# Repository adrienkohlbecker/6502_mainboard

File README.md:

# 6502 mainboard

## Board

## Schematic

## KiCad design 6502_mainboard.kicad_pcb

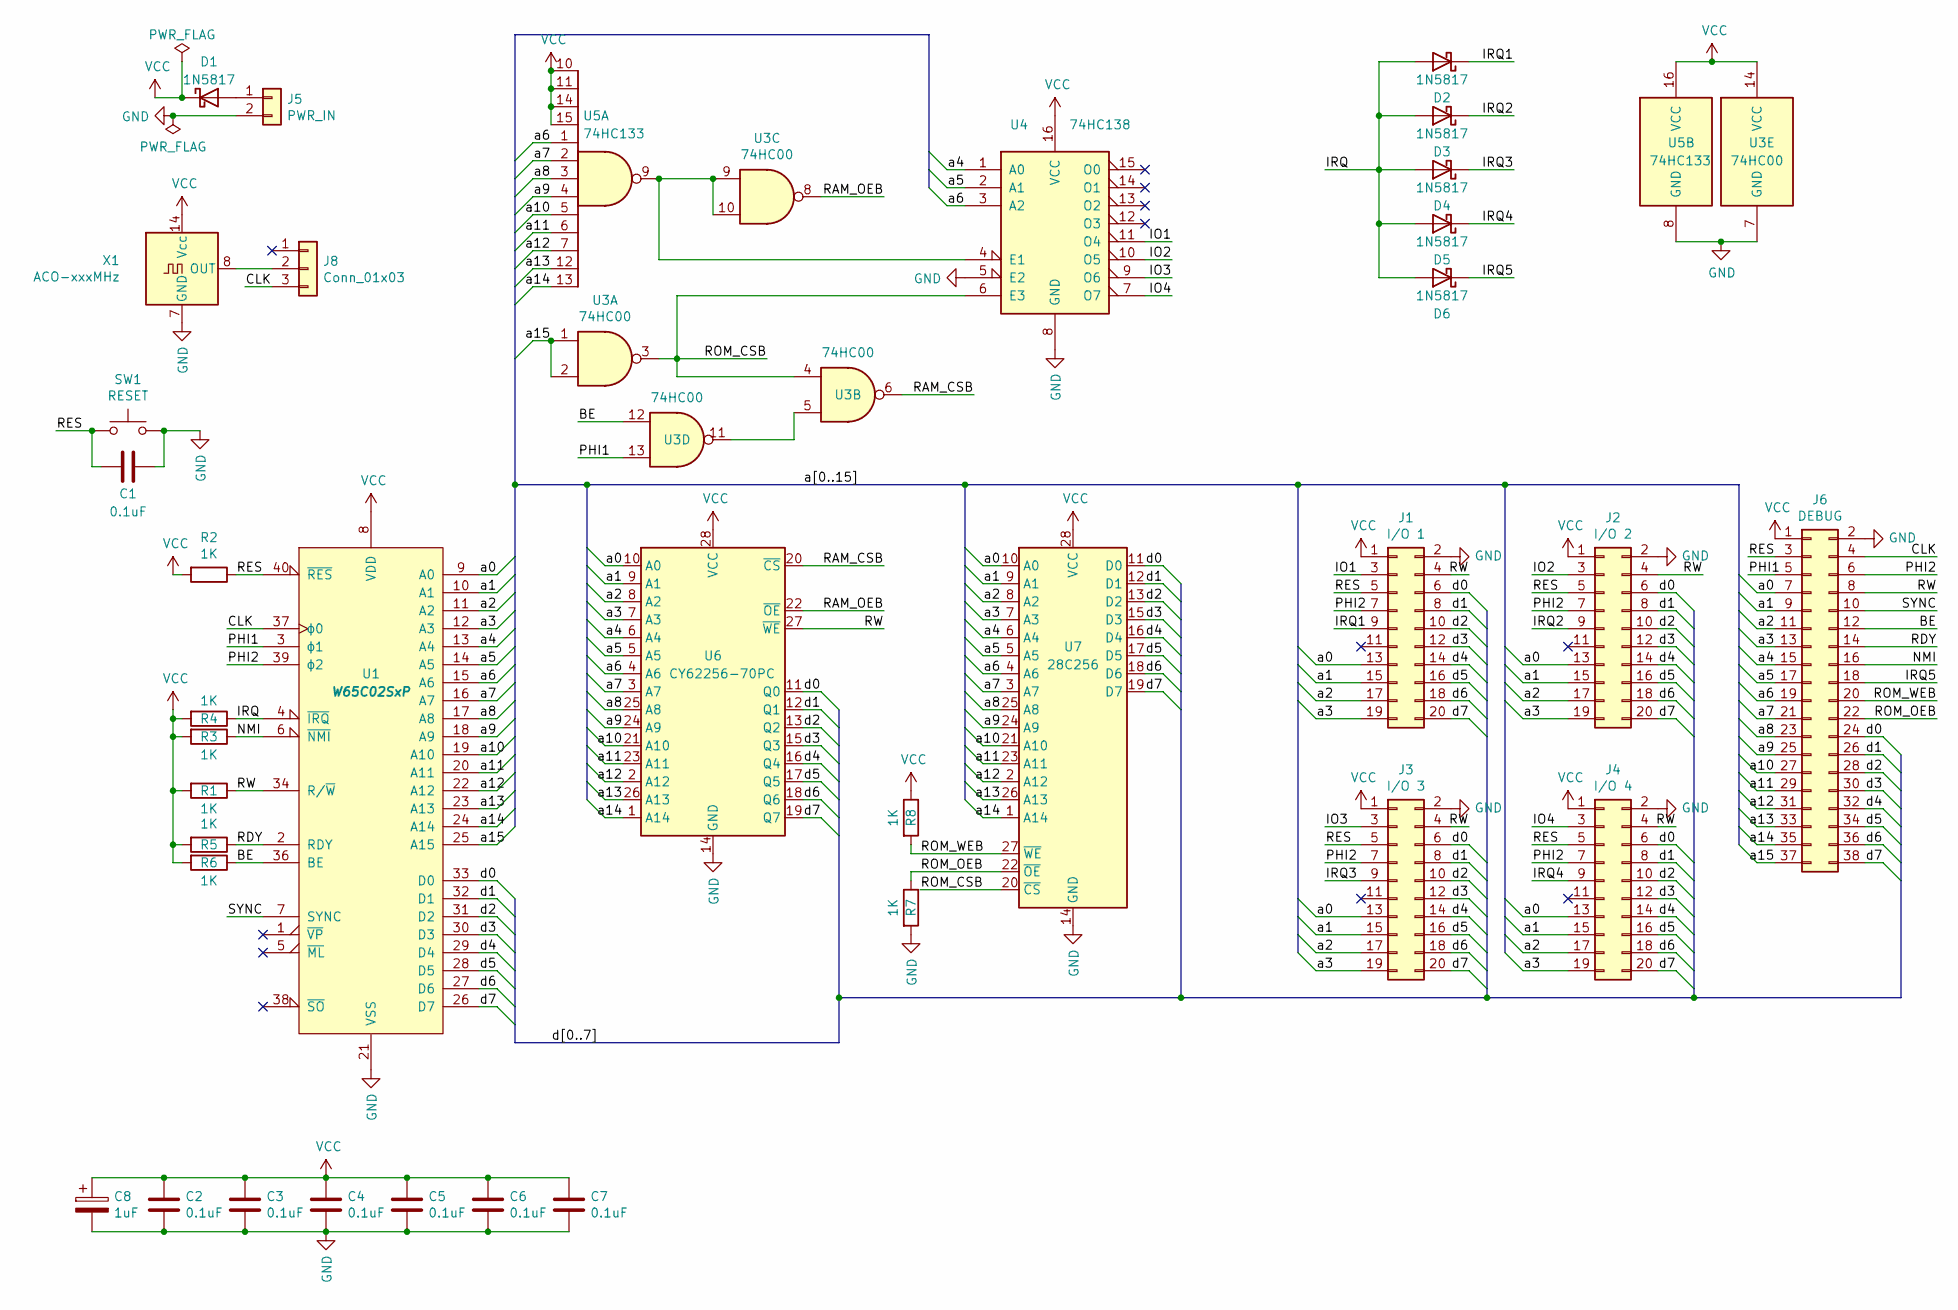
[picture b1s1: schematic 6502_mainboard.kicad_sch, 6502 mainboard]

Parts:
C1, C2, C3, C4, C5, C6, C7: 0.1uF; C_Disc_D3.0mm_W1.6mm_P2.50mm
C8: 1uF; CP_Radial_D4.0mm_P2.00mm
D1, D2, D3, D4, D5, D6: 1N5817; D_DO-35_SOD27_P7.62mm_Horizontal
J1: I/O 1; PinHeader_2x10_P2.54mm_Vertical
J2: I/O 2; PinHeader_2x10_P2.54mm_Vertical
J3: I/O 3; PinHeader_2x10_P2.54mm_Vertical
J4: I/O 4; PinHeader_2x10_P2.54mm_Vertical
J5: PWR_IN; PinSocket_1x02_P2.54mm_Vertical
J6: DEBUG; PinSocket_2x19_P2.54mm_Vertical
J8: Conn_01x03; PinSocket_1x03_P2.54mm_Vertical
R1, R2, R3, R4, R5, R6, R7, R8: 1K; R_Axial_DIN0207_L6.3mm_D2.5mm_P7.62mm_Horizontal
SW1: RESET; SW_PUSH_6mm
U1: W65C02SxP; DIP-40_W15.24mm
U3: 74HC00; DIP-14_W7.62mm
U4: 74HC138; DIP-16_W7.62mm
U5: 74HC133; DIP-16_W7.62mm
U6: CY62256-70PC; DIP-28_W15.24mm
U7: 28C256; DIP_Socket-28_W11.9_W12.7_W15.24_W17.78_W18.5_3M_228-1277-0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
X1: ACO-xxxMHz; Oscillator_DIP-14

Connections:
/a0: J1.13, J2.13, J3.13, J4.13, J6.7, U1.9 (A0), U6.10 (A0), U7.10 (A0)
/a1: J1.15, J2.15, J3.15, J4.15, J6.9, U1.10 (A1), U6.9 (A1), U7.9 (A1)
/a2: J1.17, J2.17, J3.17, J4.17, J6.11, U1.11 (A2), U6.8 (A2), U7.8 (A2)
/a3: J1.19, J2.19, J3.19, J4.19, J6.13, U1.12 (A3), U6.7 (A3), U7.7 (A3)
/a4: J6.15, U1.13 (A4), U4.1 (A0), U6.6 (A4), U7.6 (A4)
/a5: J6.17, U1.14 (A5), U4.2 (A1), U6.5 (A5), U7.5 (A5)
/a6: J6.19, U1.15 (A6), U4.3 (A2), U5.1, U6.4 (A6), U7.4 (A6)
/a7: J6.21, U1.16 (A7), U5.2, U6.3 (A7), U7.3 (A7)
/a8: J6.23, U1.17 (A8), U5.3, U6.25 (A8), U7.25 (A8)
/a9: J6.25, U1.18 (A9), U5.4, U6.24 (A9), U7.24 (A9)
/a10: J6.27, U1.19 (A10), U5.5, U6.21 (A10), U7.21 (A10)
/a11: J6.29, U1.20 (A11), U5.6, U6.23 (A11), U7.23 (A11)
/a12: J6.31, U1.22 (A12), U5.7, U6.2 (A12), U7.2 (A12)
/a13: J6.33, U1.23 (A13), U5.12, U6.26 (A13), U7.26 (A13)
/a14: J6.35, U1.24 (A14), U5.13, U6.1 (A14), U7.1 (A14)
/a15: J6.37, U1.25 (A15), U3.1, U3.2
/d0: J1.6, J2.6, J3.6, J4.6, J6.24, U1.33 (D0), U6.11 (Q0), U7.11 (D0)
/d1: J1.8, J2.8, J3.8, J4.8, J6.26, U1.32 (D1), U6.12 (Q1), U7.12 (D1)
/d2: J1.10, J2.10, J3.10, J4.10, J6.28, U1.31 (D2), U6.13 (Q2), U7.13 (D2)
/d3: J1.12, J2.12, J3.12, J4.12, J6.30, U1.30 (D3), U6.15 (Q3), U7.15 (D3)
/d4: J1.14, J2.14, J3.14, J4.14, J6.32, U1.29 (D4), U6.16 (Q4), U7.16 (D4)
/d5: J1.16, J2.16, J3.16, J4.16, J6.34, U1.28 (D5), U6.17 (Q5), U7.17 (D5)
/d6: J1.18, J2.18, J3.18, J4.18, J6.36, U1.27 (D6), U6.18 (Q6), U7.18 (D6)
/d7: J1.20, J2.20, J3.20, J4.20, J6.38, U1.26 (D7), U6.19 (Q7), U7.19 (D7)
BE: J6.12, R6.1, U1.36 (BE), U3.12
CLK: J6.4, J8.3, U1.37 (ϕ0)
GND: C1.1, C2.2, C3.2, C4.2, C5.2, C6.2, C7.2, C8.2, J1.2, J2.2, J3.2, J4.2, J5.2, J6.2, R7.2, SW1.2, U1.21 (VSS), U3.7 (GND), U4.5 (E2), U4.8 (GND), U5.8 (GND), U6.14 (GND), U7.14 (GND), X1.7 (GND)
IO1: J1.3, U4.11 (O4)
IO2: J2.3, U4.10 (O5)
IO3: J3.3, U4.9 (O6)
IO4: J4.3, U4.7 (O7)
IRQ: D2.2 (A), D3.2 (A), D4.2 (A), D5.2 (A), D6.2 (A), R4.1, U1.4 (~IRQ)
IRQ1: D2.1 (K), J1.9
IRQ2: D3.1 (K), J2.9
IRQ3: D4.1 (K), J3.9
IRQ4: D5.1 (K), J4.9
IRQ5: D6.1 (K), J6.18
NMI: J6.16, R3.1, U1.6 (~NMI)
unnamed: D1.2 (A), J5.1
unnamed: J8.2, X1.8 (OUT)
unnamed: U3.9, U3.10, U4.4 (E1), U5.9
unnamed: U3.5, U3.11
PHI1: J6.5, U1.3 (ϕ1), U3.13
PHI2: J1.7, J2.7, J3.7, J4.7, J6.6, U1.39 (ϕ2)
RAM_CSB: U3.6, U6.20 (~CS)
RAM_OEB: U3.8, U6.22 (~OE)
RDY: J6.14, R1.1, U1.2 (RDY)
RES: C1.2, J1.5, J2.5, J3.5, J4.5, J6.3, R2.1, SW1.1, U1.40 (~RES)
ROM_CSB: U3.3, U3.4, U4.6 (E3), U7.20 (~CS)
ROM_OEB: J6.22, R7.1, U7.22 (~OE)
ROM_WEB: J6.20, R8.2, U7.27 (~WE)
RW: J1.4, J2.4, J3.4, J4.4, J6.8, R5.1, U1.34 (R/~W), U6.27 (~WE)
SYNC: J6.10, U1.7 (SYNC)
VCC: C2.1, C3.1, C4.1, C5.1, C6.1, C7.1, C8.1, D1.1 (K), J1.1, J2.1, J3.1, J4.1, J6.1, R1.2, R2.2, R3.2, R4.2, R5.2, R6.2, R8.1, U1.8 (VDD), U3.14 (VCC), U4.16 (VCC), U5.10, U5.11, U5.14, U5.15, U5.16 (VCC), U6.28 (VCC), U7.28 (VCC), X1.14 (Vcc)

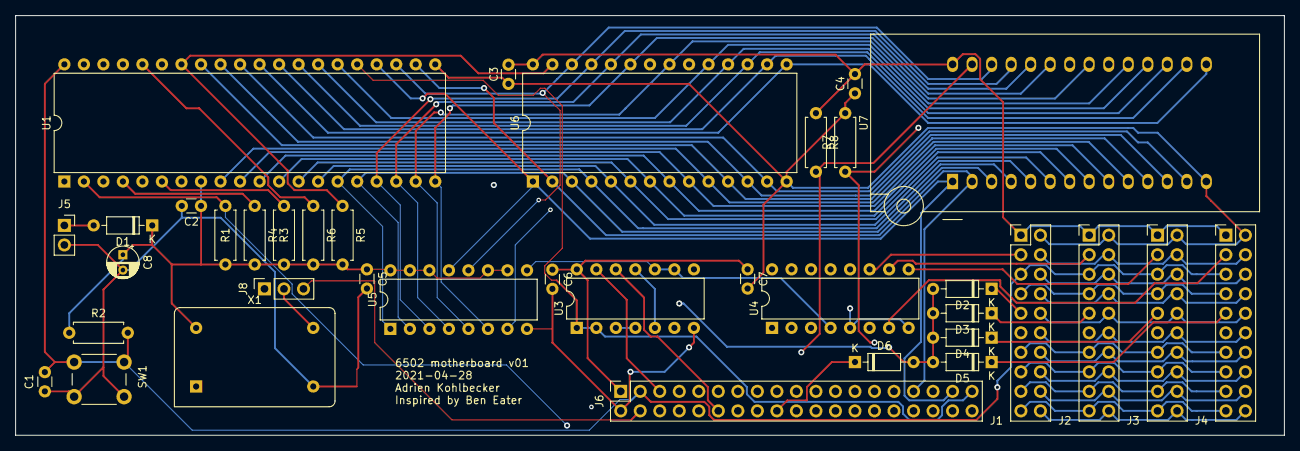
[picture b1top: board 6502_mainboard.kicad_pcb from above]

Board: 4 copper layers, 165.1 x 54.6 mm, 37 parts (0 on the bottom side), 54 nets.

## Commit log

2021-05-18 Add mainboard v1
2021-12-19 Remove ignored files
2023-06-07 Update for KiCad 6
